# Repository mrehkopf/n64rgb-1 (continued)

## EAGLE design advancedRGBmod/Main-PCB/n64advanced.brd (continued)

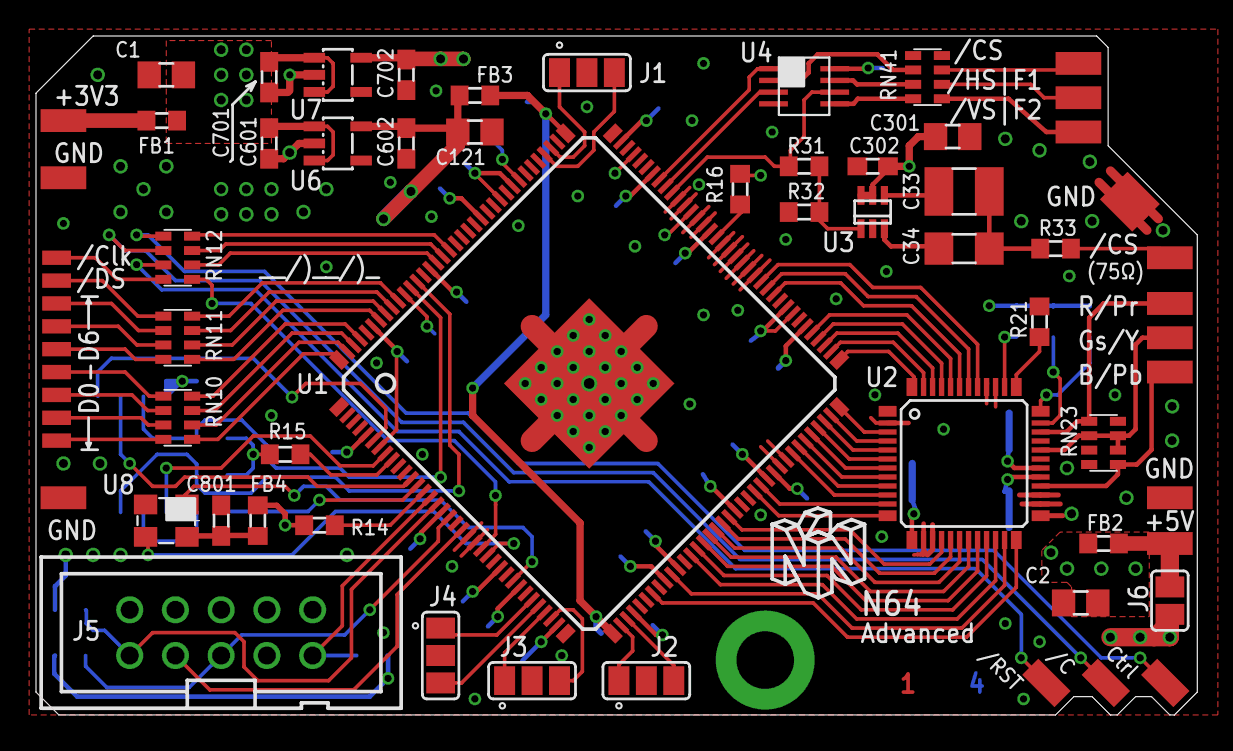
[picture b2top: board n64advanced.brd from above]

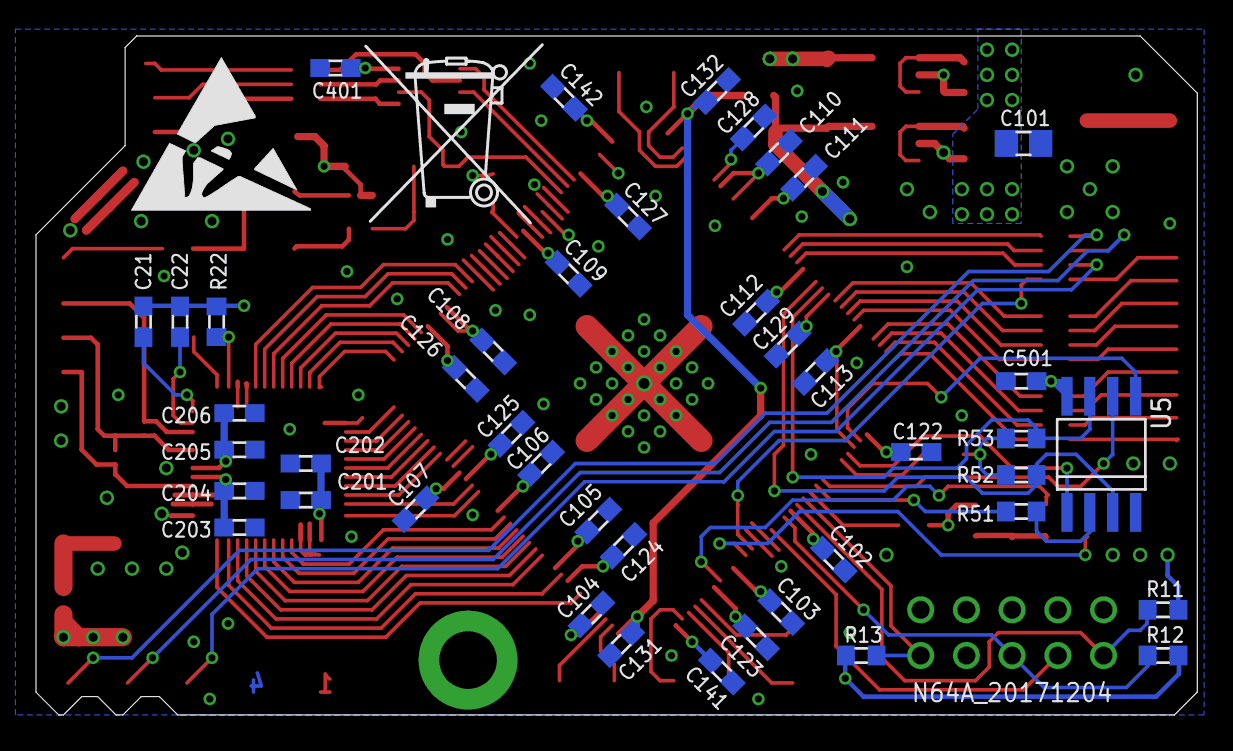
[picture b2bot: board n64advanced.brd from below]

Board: 4 copper layers, 64.5 x 37.7 mm, 112 parts (45 on the bottom side), 105 nets.

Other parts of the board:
U$1: ESD_10.00
U$2: MUELLTONNE_10.00

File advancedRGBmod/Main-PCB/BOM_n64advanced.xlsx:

Designator | MPN | QTY | DESCRIPTION | VALUE | PACKAGE | NOTES | Digikey | Mouser
U1 | 10CL010YE144C8G | 1 | Cyclone 10 LP FPGA, 10k LE |  | EQFP144 | can be replaced with other FPGAs on demand (see Schematic file) | https://www.digikey.de/product-detail/en/altera/10CL010YE144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 | http://www.mouser.de/ProductDetail/Intel/10CL010YE144C8G/
U2 | ADV7125KSTZ140 | 1 | Video DAC 8bit, 3Ch. |  | 48-LQFP | can be replaced with ADV7123KSTZ140 on demand | https://www.digikey.de/product-detail/de/analog-devices-inc/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 | www.mouser.de/ProductDetail/Analog-Devices/ADV7125KSTZ140/
U3 | TSH122ICT | 1 | Video Verstärker 1Ch |  | SC-70-6 |  | https://www.digikey.de/product-detail/de/stmicroelectronics/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 | http://www.mouser.de/ProductDetail/STMicroelectronics/TSH122ICT/
U4 | SN74LVC3G17DCTR | 1 | Non-Inv Buffer 3Ch., Schmitt Trigger |  | 8-LSSOP, 8-MSOP | TI: DCT Package Footprint | https://www.digikey.de/product-detail/de/texas-instruments/S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 | http://www.mouser.de/ProductDetail/Texas-Instruments/SN74LVC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
U5 | S25FL116K0XMFB013 | 1 | IC FLASH 16MBIT 108MHZ 8SOIC |  | 8-SOIC | 208mil Body; Digikey ist Alternative im 150mil Body. Footprint ünterstützt beid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 | https://www.digikey.de/product-detail/de/cypress-semiconduct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 | http://www.mouser.de/ProductDetail/Cypress/S25FL116K0XMFB013/
U6 | TLV70012DDCR | 1 | LDO 1.2V |  | SOT-23-5 |  | https://www.digikey.de/product-detail/de/texas-instruments/T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 | http://www.mouser.de/ProductDetail/Texas-Instruments/TLV70012DDCR/
U7 | TLV70025DDCR | 1 | LDO 2.5V |  | SOT-23-5 |  | https://www.digikey.de/product-detail/de/texas-instruments/T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 | http://www.mouser.de/ProductDetail/Texas-Instruments/TLV70025DDCR/
U8 | ASE-50.000MHZ-LC-T | 1 | OSC 50MHz | 50MHz | 4-SMD | L x B: 0,126" x 0,098" (3,20 mm x 2,50 mm) | https://www.digikey.de/product-detail/de/abracon-llc/ASE-50.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 | http://www.mouser.de/ProductDetail/ABRACON/ASE-50000MHZ-L-C-T/
C1,C2 | GRM219R60J476ME44D | 2 | Ceramic capacitor, X5R | 47uF / 6.3V | SMD0805 |  | https://www.digikey.de/product-detail/de/murata-electronics-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 | http://www.mouser.de/ProductDetail/Murata/GRM219R60J476ME44D/
C21,C22,C102,C103,C104,C105,C106,C107,C108,C109,C110,C111,C112,C113,C122,C123,C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 | GRM188R71H104KA93J | 31 | Ceramic capacitor, X7R | 0.1uF / 50V | SMD0603 |  | https://www.digikey.de/product-detail/de/murata-electronics-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 | http://www.mouser.de/ProductDetail/Murata/GRM188R71H104KA93J/
C101,C121,C301 | GRM21BR60J106ME19L | 3 | Ceramic capacitor, X5R | 10uF / 6.3V | SMD0805 |  | https://www.digikey.de/product-detail/de/murata-electronics-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 | http://www.mouser.de/ProductDetail/Murata/GRM21BR60J106ME19L/
C202,C204,C206,C302,C801 | GRM188R70J103KA01D | 5 | Ceramic capacitor, X7R | 0.01uF / 50V | SMD0603 |  | https://www.digikey.de/product-detail/de/murata-electronics-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 | http://www.mouser.de/ProductDetail/Murata/GRM188R70J103KA01D/
C33 | GRM32DR60J336ME19L | 1 | Ceramic capacitor, X5R | 33uF / 6.3V | SMD1210 |  | https://www.digikey.de/product-detail/de/murata-electronics-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 | http://www.mouser.de/ProductDetail/Murata-Electronics/GRM32D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
C34 | GRM31CR60J226KE19L | 1 | Ceramic capacitor, X5R | 22uF / 6.3V | SMD1206 |  | https://www.digikey.de/product-detail/de/murata-electronics-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 | http://www.mouser.de/ProductDetail/Murata/GRM31CR60J226KE19L/
C601,C602,C701,C702 | GRM18R60J105KA01J | 4 | Ceramic capacitor, X5R | 1uF / 6.3V | SMD0603 |  | https://www.digikey.de/product-detail/de/murata-electronics-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 | https://www.mouser.de/ProductDetail/Murata/GRM188R60J105KA01J/
FB1,FB2,FB3,FB4 | MPZ1608S221A | 4 | Ferrit bead, power line |  | SMD0603 |  | https://www.digikey.de/product-detail/de/tdk-corporation/MPZ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 | http://www.mouser.de/ProductDetail/TDK/MPZ1608S221A/
J5 | 30310-6002HB | 1 |  |  |  | JTAG Connector | https://www.digikey.de/product-detail/de/3m/30310-6002HB/303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 | http://www.mouser.de/ProductDetail/3M/30310-6002HB/
R11 | RC0603FR-071KL | 1 | Resistor | 1k | SMD0603 |  | https://www.digikey.de/product-detail/de/yageo/RC0603FR-071K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 | http://www.mouser.de/ProductDetail/Yageo/RC0603FR-071KL/
R12,R13,R14,R15,R16 | RC0603FR-0710KL | 5 | Resistor | 10k | SMD0603 |  | https://www.digikey.de/product-detail/de/yageo/RC0603FR-0710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 | http://www.mouser.de/ProductDetail/Yageo/RC0603FR-0710KL/
R21 | RC0603FR-07523RL | 1 | Resistor | 518 | SMD0603 | with ADV7123: use 516ohm resistor; for PAL-Standard: 528ohm/527ohm | https://www.digikey.de/product-detail/de/yageo/RC0603FR-0752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 | http://www.mouser.de/ProductDetail/Yageo/RC0603FR-07523RL/
R22,R31,R52,R53 | RC0603FR-074K7L | 4 | Resistor | 4k7 | SMD0603 |  | https://www.digikey.de/product-detail/de/yageo/RC0603FR-074K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 | http://www.mouser.de/ProductDetail/Yageo/RC0603FR-074K7L/
R32 | RC0603FR-07475RL | 1 | Resistor | 475 | SMD0603 |  | https://www.digikey.de/product-detail/de/yageo/RC0603FR-0747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 | http://www.mouser.de/ProductDetail/Yageo/RC0603FR-07475RL/
R33 | RC0603FR-0775RL | 1 | Resistor | 75 | SMD0603 |  | https://www.digikey.de/product-detail/de/yageo/RC0603FR-0775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 | http://www.mouser.de/ProductDetail/Yageo/RC0603FR-0775RL/
R51 | RC0603FR-0724R9L | 1 | Resistor | 25 | SMD0603 |  | https://www.digikey.de/product-detail/de/yageo/RC0603FR-0724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 | http://www.mouser.de/ProductDetail/Yageo/RC0603FR-0724R9L/
RN10,RN11,RN12 | CAT16-47R0F4LF | 3 | Resistor Array (4x) | 47 | SMD1206 | Alternative: CAY16-47R0F4LF | https://www.digikey.de/product-detail/de/bourns-inc/CAT16-47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 | http://www.mouser.de/ProductDetail/Bourns/CAT16-47R0F4LF/
RN23,RN41 | CAT16-75R0F4LF | 2 | Resistor Array (4x) | 75 | SMD1206 | Alternative: CAY16-75R0F4LF; Digi-Key Link zur J4LF Serie (5% Toleranz statt 1%) | https://www.digikey.de/product-detail/de/bourns-inc/CAT16-75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 | http://www.mouser.de/search/ProductDetail.aspx?R=0virtualkey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

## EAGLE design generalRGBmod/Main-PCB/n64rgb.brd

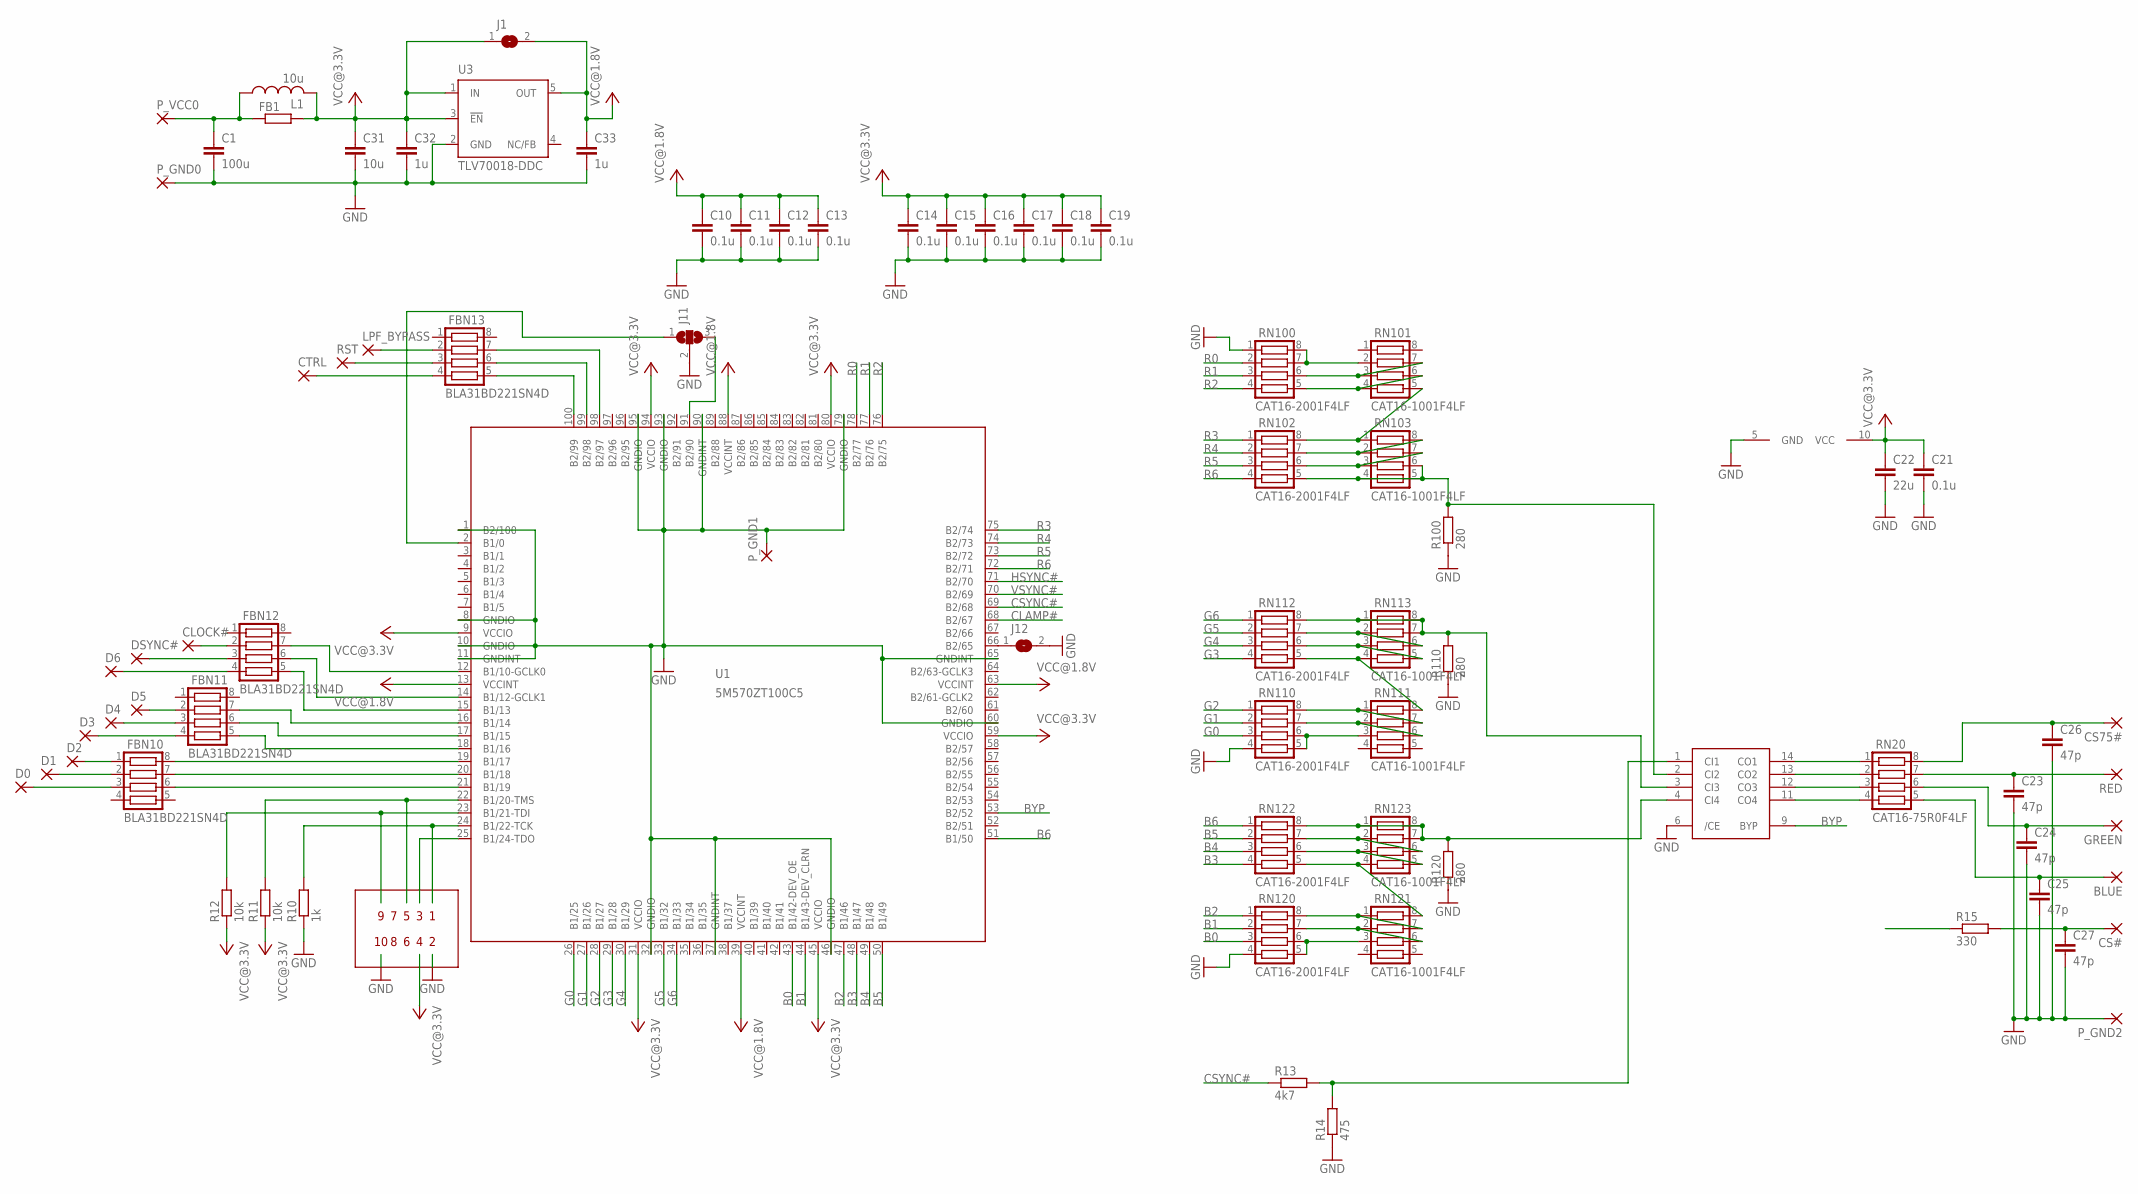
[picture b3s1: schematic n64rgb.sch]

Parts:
BLUE: SMD2; SMD1,27-2,54
C1: 100u; C1206K
C10, C11, C12, C13, C14, C15, C16, C17, C18, C19, C21: 0.1u; C0603
C22: 22u; C1206K
C23, C24, C25, C26, C27: 47p; C0603
C31: 10u; C1206K
C32, C33: 1u; C0603
CLOCK#: SMD1; SMD0,8-1,6
CS75#: SMD2; SMD1,27-2,54
CS#: SMD2; SMD1,27-2,54
CTRL: SMD2; SMD1,27-2,54
D0, D1, D2, D3, D4, D5, D6: SMD1; SMD0,8-1,6
DSYNC#: SMD1; SMD0,8-1,6
FB1: R-EU_R0603; R0603
FBN10, FBN11, FBN12, FBN13: BLA31BD221SN4D; CTS742C083
GREEN: SMD2; SMD1,27-2,54
J1, J12: SJ
J11: SJ2W; SJ_2
L1: 10u; L3230M
LPF_BYPASS: SMD2; SMD1,27-2,54
P_GND0, P_GND1, P_GND2: SMD2; SMD1,27-2,54
P_VCC0: SMD2; SMD1,27-2,54
R10: 1k; R0603
R11, R12: 10k; R0603
R13: 4k7; R0603
R14: 475; R0603
R15: 330; R0603
R100, R110, R120: 280; R0603
RED: SMD2; SMD1,27-2,54
RN20: CAT16-75R0F4LF; CTS742C083
RN100, RN102, RN110, RN112, RN120, RN122: CAT16-2001F4LF; CTS742C083
RN101, RN103, RN111, RN113, RN121, RN123: CAT16-1001F4LF; CTS742C083
RST: SMD2; SMD1,27-2,54
U1: 5M570ZT100C5; TQFP100
U2: THS7374
U3: TLV70018-DDC; SOT23-DBV

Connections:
B0: RN120.3, U1.43 (B1/42-DEV_OE)
B1: RN120.2, U1.44 (B1/43-DEV_CLRN)
B2: RN120.1, U1.47 (B1/46)
B3: RN122.4, U1.48 (B1/47)
B4: RN122.3, U1.49 (B1/48)
B5: RN122.2, U1.50 (B1/49)
B6: RN122.1, U1.51 (B1/50)
BYP: U1.53 (B2/52), U2.9 (BYP)
CLAMP#: U1.68 (B2/67)
CSYNC#: R13.1, R15.1, U1.69 (B2/68)
G0: RN110.3, U1.26 (B1/25)
G1: RN110.2, U1.27 (B1/26)
G2: RN110.1, U1.28 (B1/27)
G3: RN112.4, U1.29 (B1/28)
G4: RN112.3, U1.30 (B1/29)
G5: RN112.2, U1.33 (B1/32)
G6: RN112.1, U1.34 (B1/33)
GND: C1.2, C10.2, C11.2, C12.2, C13.2, C14.2, C15.2, C16.2, C17.2, C18.2, C19.2, C21.2, C22.2, C23.2, C24.2, C25.2, C26.2, C27.2, C31.2, C32.2, C33.2, J11.2, J12.2, P_GND0.1, P_GND1.1, P_GND2.1, R10.1, R14.1, R100.1, R110.1, R120.1, RN100.1, RN110.4, RN120.4, U1.1 (B2/100), U1.8 (GNDIO), U1.10 (GNDIO), U1.11 (GNDINT), U1.32 (GNDIO), U1.37 (GNDINT), U1.46 (GNDIO), U1.60 (GNDIO), U1.65 (GNDINT), U1.79 (GNDIO), U1.90 (GNDINT), U1.93 (GNDIO), U1.95 (GNDIO), U2.5 (GND), U2.6 (/CE), U3.2 (GND)
HSYNC#: U1.71 (B2/70)
unnamed: R13.2, R14.2, U2.1 (CI1)
unnamed: C23.1, RED.1, RN20.7
unnamed: RN20.1, U2.14 (CO1)
unnamed: RN20.2, U2.13 (CO2)
unnamed: RN20.3, U2.12 (CO3)
unnamed: RN20.4, U2.11 (CO4)
unnamed: CTRL.1, FBN13.4
unnamed: FBN13.3, RST.1
unnamed: FBN13.2, LPF_BYPASS.1
unnamed: C24.1, GREEN.1, RN20.6
unnamed: BLUE.1, C25.1, RN20.5
unnamed: C26.1, CS75#.1, RN20.8
unnamed: C27.1, CS#.1, R15.2
unnamed: FBN13.5, U1.100 (B2/99)
unnamed: D1.P$1, FBN10.2
unnamed: D0.P$1, FBN10.3
unnamed: D2.P$1, FBN10.1
unnamed: FBN10.6, U1.21 (B1/19)
unnamed: FBN10.7, U1.20 (B1/18)
unnamed: FBN10.8, U1.19 (B1/17)
unnamed: D3.P$1, FBN11.4
unnamed: D4.P$1, FBN11.3
unnamed: D5.P$1, FBN11.2
unnamed: D6.P$1, FBN12.4
unnamed: RN110.5, RN110.6, RN111.3
unnamed: RN110.7, RN111.2, RN111.6
unnamed: RN110.8, RN111.1, RN111.7
unnamed: RN111.8, RN112.5, RN113.4
unnamed: RN112.6, RN113.3, RN113.5
unnamed: RN112.7, RN113.2, RN113.6
unnamed: R120.2, RN122.8, RN123.1, RN123.7, RN123.8, U2.4 (CI4)
unnamed: RN120.5, RN120.6, RN121.3
unnamed: RN120.7, RN121.2, RN121.6
unnamed: RN120.8, RN121.1, RN121.7
unnamed: RN121.8, RN122.5, RN123.4
unnamed: DSYNC#.P$1, FBN12.3
unnamed: RN122.6, RN123.3, RN123.5
unnamed: RN122.7, RN123.2, RN123.6
unnamed: CLOCK#.P$1, FBN12.2
unnamed: FBN11.5, U1.18 (B1/16)
unnamed: FBN11.6, U1.17 (B1/15)
unnamed: FBN11.7, U1.16 (B1/14)
unnamed: FBN12.5, U1.15 (B1/13)
unnamed: FBN12.6, U1.14 (B1/12-GCLK1)
unnamed: FBN12.7, U1.12 (B1/10-GCLK0)
unnamed: FBN13.6, U1.99 (B2/98)
unnamed: FBN13.7, U1.98 (B2/97)
unnamed: R100.2, RN102.5, RN103.4, RN103.5, RN103.6, U2.2 (CI2)
unnamed: J12.1, U1.66 (B2/65)
unnamed: J11.3, U1.91 (B2/90)
unnamed: J11.1, U1.2 (B1/0)
unnamed: C1.1, FB1.1, L1.1, P_VCC0.1
unnamed: R110.2, RN112.8, RN113.1, RN113.7, RN113.8, U2.3 (CI3)
unnamed: RN100.7, RN100.8, RN101.2
unnamed: RN100.6, RN101.3, RN101.7
unnamed: RN100.5, RN101.4, RN101.6
unnamed: RN101.5, RN102.8, RN103.1
unnamed: RN102.7, RN103.2, RN103.8
unnamed: RN102.6, RN103.3, RN103.7
R0: RN100.2, U1.78 (B2/77)
R1: RN100.3, U1.77 (B2/76)
R2: RN100.4, U1.76 (B2/75)
R3: RN102.1, U1.75 (B2/74)
R4: RN102.2, U1.74 (B2/73)
R5: RN102.3, U1.73 (B2/72)
R6: RN102.4, U1.72 (B2/71)
TCK: R10.2, U1.24 (B1/22-TCK)
TDI: R12.2, U1.23 (B1/21-TDI)
TDO: U1.25 (B1/24-TDO)
TMS: R11.2, U1.22 (B1/20-TMS)
VCC@1.8V: C10.1, C11.1, C12.1, C13.1, C33.1, J1.2, U1.13 (VCCINT), U1.39 (VCCINT), U1.63 (VCCINT), U1.88 (VCCINT), U3.5 (OUT)
VCC@3.3V: C14.1, C15.1, C16.1, C17.1, C18.1, C19.1, C21.1, C22.1, C31.1, C32.1, FB1.2, J1.1, L1.2, R11.1, R12.1, U1.9 (VCCIO), U1.31 (VCCIO), U1.45 (VCCIO), U1.59 (VCCIO), U1.80 (VCCIO), U1.94 (VCCIO), U2.10 (VCC), U3.1 (IN), U3.3 (!EN)
VSYNC#: U1.70 (B2/69)

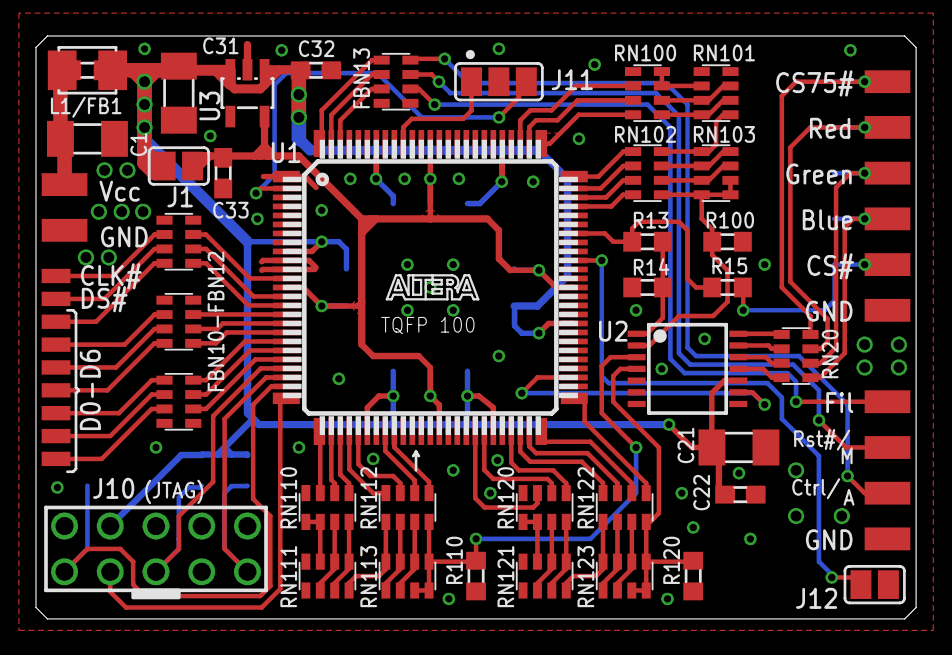
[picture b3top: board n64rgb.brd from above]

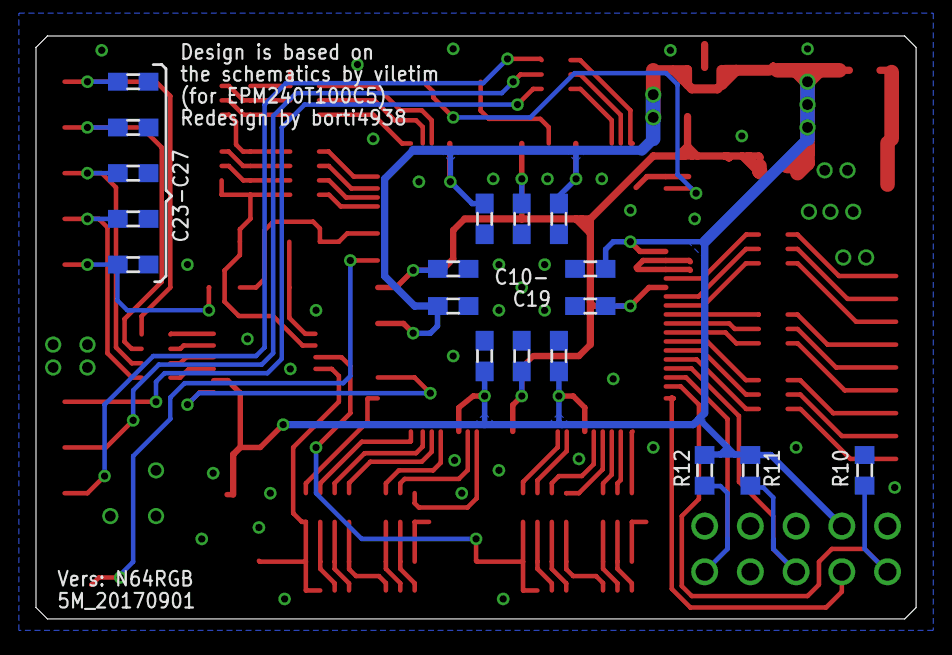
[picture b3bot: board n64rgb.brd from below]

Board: 2 copper layers, 48.9 x 32.4 mm, 76 parts (18 on the bottom side), 88 nets.

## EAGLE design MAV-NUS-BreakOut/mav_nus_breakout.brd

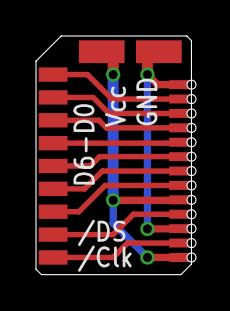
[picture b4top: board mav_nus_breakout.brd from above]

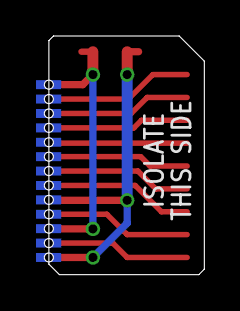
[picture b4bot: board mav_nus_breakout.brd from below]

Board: 2 copper layers, 8.6 x 13.3 mm, 37 parts (13 on the bottom side), 11 nets.

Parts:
PAD13, PAD14: SMD1,27-2,54
U$211, U$212, U$213, U$214, U$215, U$222, U$226, U$227, U$228, U$229, U$230, U$231, U$232, U$233, U$234, U$235, U$236, U$237, U$238, U$239, U$240, U$241, U$242, U$243, U$244, U$245: SMD0,45; SMD0,5-1,4
U$216, U$217, U$218, U$219, U$220, U$221, U$223, U$224, U$225: SMD1; SMD0,8-1,6

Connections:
unnamed: U$211.P$1, U$216.P$1
unnamed: U$217.P$1, U$222.P$1
unnamed: U$218.P$1, U$226.P$1
unnamed: U$219.P$1, U$227.P$1
unnamed: U$220.P$1, U$228.P$1
unnamed: U$221.P$1, U$229.P$1
unnamed: U$223.P$1, U$230.P$1
unnamed: U$224.P$1, U$231.P$1
unnamed: U$225.P$1, U$232.P$1
unnamed: PAD13.1, U$212.P$1, U$213.P$1
unnamed: PAD14.1, U$214.P$1, U$215.P$1

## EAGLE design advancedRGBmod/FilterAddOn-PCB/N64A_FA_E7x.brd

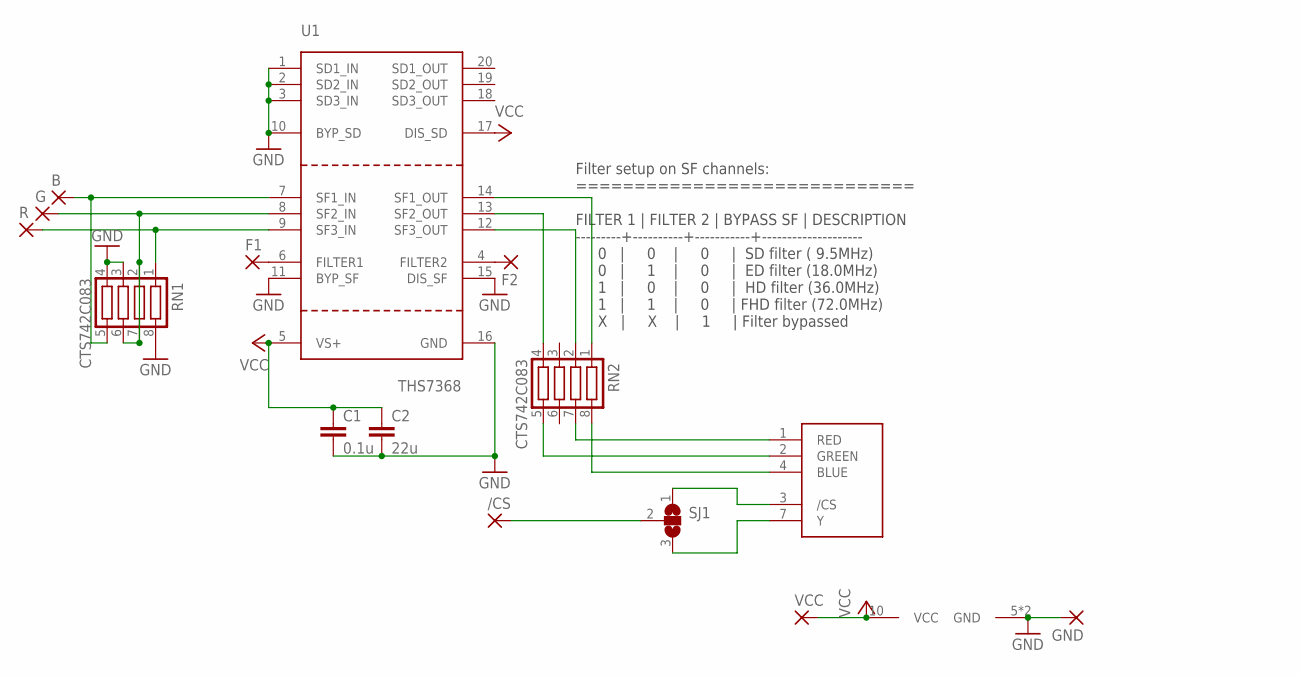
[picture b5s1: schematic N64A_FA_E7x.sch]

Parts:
/CS: SMD2; SMD1,27-2,54
B: SMD2; SMD1,27-2,54
C1: 0.1u; C0603
C2: 22u; C1206
F1, F2: SMD1; SMD0,8-1,6
G: SMD2; SMD1,27-2,54
GND: SMD2; SMD1,27-2,54
R: SMD2; SMD1,27-2,54
RN1, RN2: CTS742C083
SJ1: SJ2W; SJ_2
U1: THS7368
U$1: SNES_MULTIAV_RGBSY
VCC: SMD2; SMD1,27-2,54

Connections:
GND: C1.2, C2.2, GND.1, RN1.3, RN1.4, RN1.8, U1.1 (SD1_IN), U1.2 (SD2_IN), U1.3 (SD3_IN), U1.10 (BYP_SD), U1.11 (BYP_SF), U1.15 (DIS_SF), U1.16 (GND), U$1.5 (GND), U$1.6 (GND)
unnamed: RN2.7, U$1.1 (RED)
unnamed: RN2.8, U$1.4 (BLUE)
unnamed: RN2.5, U$1.2 (GREEN)
unnamed: RN2.4, U1.13 (SF2_OUT)
unnamed: RN2.1, U1.14 (SF1_OUT)
unnamed: RN2.2, U1.12 (SF3_OUT)
unnamed: SJ1.1, U$1.3 (/CS)
unnamed: F1.P$1, U1.6 (FILTER1)
unnamed: R.1, RN1.1, U1.9 (SF3_IN)
unnamed: G.1, RN1.2, RN1.6, RN1.7, U1.8 (SF2_IN)
unnamed: F2.P$1, U1.4 (FILTER2)
unnamed: /CS.1, SJ1.2
unnamed: B.1, RN1.5, U1.7 (SF1_IN)
unnamed: SJ1.3, U$1.7 (Y)
VCC: C1.1, C2.1, U1.5 (VS+), U1.17 (DIS_SD), U$1.10 (VCC), VCC.1

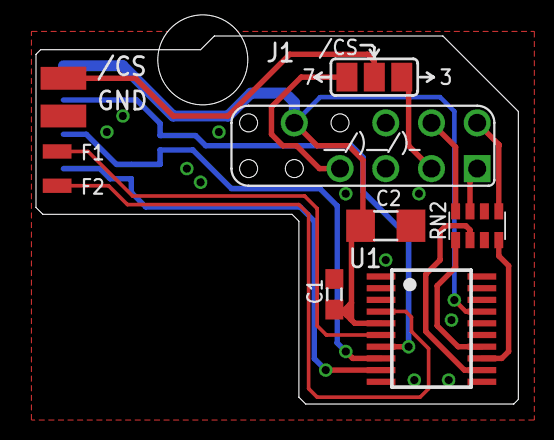
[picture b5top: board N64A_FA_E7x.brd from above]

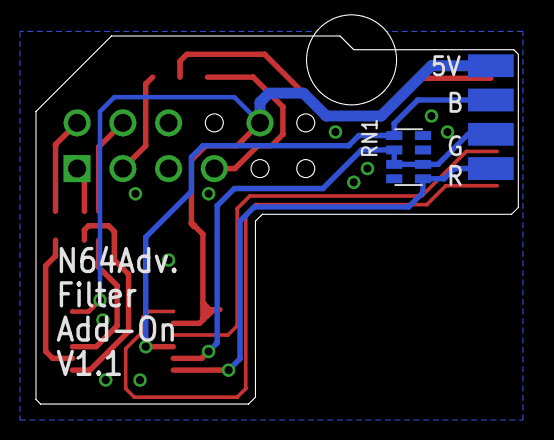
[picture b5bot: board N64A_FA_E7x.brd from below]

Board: 2 copper layers, 26.8 x 20.4 mm, 15 parts (5 on the bottom side), 16 nets.

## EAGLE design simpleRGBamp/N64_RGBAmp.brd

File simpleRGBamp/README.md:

# Simple RGB Mod

## General Information

Technical information about this mod...

- Which N64 is suitable for it
- How to install this mod

... can be found on RetroRGB.com ([Compatibility](http://www.retrorgb.com/n64rgbcompatible.html) and [Installation](http://www.retrorgb.com/n64rgbmod.html))

Many thanks to Bob at this place for sharing that.

The rest

- Which parts are needed
- Some additional tips and hints

can be found in this document.

## Components

**be aware of the additional comments below this table**

| Label | Device / Part | Package | Quantity | Mouser Ordering Key | Comment |
|:---:|---|---|:---:|:---|---|
| | | | | | |
| **U1** | THS7374 | TSSOP-14 | 1 | 595-THS7374IPWR | |
| | THS7373 | TSSOP-14 | 1 | 595-THS7373IPWR | **Alternative** for the THS7374 [1] |
| **C1** | 22uF / 6.3V (tantal) | SMD case B (typical: 3.50mm x 2.80mm) | 1 | 74-593D226X96R3B2TE3 | |
| **C2** | 0.1uF / 50V (10%) | SMD 0603 | 1 | 80-C0603C104K9R | |  
| | | | | | |
| **R1, R41** | 4.7kohm (1%) | SMD 0603 | 2 | 71-CRCW06034K70FKEAH | |
| **R42** | 475ohm (1%) | SMD 0603 | 1 | 71-CRCW0603-475-E3 | csync compatible with 75ohm termination [2,3] |
| | 10.7kohm | SMD 0603 | 1 | 71-CRCW060310K7FKEB | TTL compatible csync [2,3] |
| **C11,C21,C31** | 0.082uF / 25V (10%) | SMD 0603 | 3 | 81-GRM188R71E823KA1D | |
| **R12,R22,R32** | 5.1Mohm (1%) | SMD 0603 | 3 | 71-CRCW06035M10FKEA | |
| | | | | | |
| **R13,R23,R33** | 75ohm (1%) | SMD 0603 | 3 | 71-RCS060375R0FKEA | NTSC-SNES RGB cable setup or direct wiring on RGB wires [4] |
| | 39ohm (1%) | SMD 0603 | 3 | 71-CRCW060339R0FKEAH | PAL-SNES cable setup on RGB wires [4] |
| **C14,C24,C34** | 47pF / 25V (5%) | SMD 0603 | 3 | 77-VJ0603A470JXXPBC | | 
| | | | | | |
| **C43** | tantal 220uF / 6.3V (tantal) | SMD case D (typical: 7.30mm x 4.30mm) | 1 | 74-593D227X96R3D2TE3 | csync compatible with 75ohm termination[2,3] |
| | 330uF / 6.3V (tantal) | SMD case D (typical: 7.30mm x 4.30mm) | 1 | 74-TR3D337K6R3E0100 | /CSYNC compatible with 75ohm termination, **Alternative** to 220uF tantal [2,3] |
| | *free* | | | | TTL compatible /CSYNC, close **J2** [2,3] |
| **R43** | 75ohm (1%) | SMD 0603 | 1 | 71-RCS060375R0FKEA | csync compatible with 75ohm termination [2,3], NTSC-SNES RGB cable setup [4] |
|| 39ohm (1%) | SMD 0603 | 1 | 71-CRCW060339R0FKEAH | /CSYNC compatible with 75ohm termination [2,3], PAL-SNES cable setup on RGB wires [4] |
| | 0ohm | SMD 0603 | 1 | *use a piece of silver wire* |  TTL compatible /CSYNC [2,3] |
| **C44** | 47pF / 25V (5%) | SMD 0603 | 1 | 77-VJ0603A470JXXPBC | [3] | 

### Additional Comments:

##### [1]  
Both ICs are supported. The THS7373 has one SD-video low pass filter (used for /CSYNC) and three HD-video filters (used for R, G and B). The THS7374 has four SD-video filters.  
At the THS7373 the HD-video LPFs can be bypassed and at the THS7374 all four SD-video filters can be bypassed (using J1).

##### [2]
According to your needs, you can design the board such that it outputs 75ohm compatible /CSYNC or TTL /CSYNC. Be aware of the components marked with this note (**R42**, **R43**, **C43/J2** and **C44**).  
If you have a RGB cable build to work with /CSYNC and use this with another (probably) _unmodified_ console, which you use on a 75ohm terminated source, you may have a resistor (and a cap) build in the sync line. Then you must build this modding board here with TTL compatible sync, too.

##### [3]
If you are going to use the stock /CSYNC circuit of the N64 - which I recommend if you have a NUS-CPU-01/02/03 board - you don't need the components **R43**, **C43** and **C44**. Just leave the footprints disassembled.  
**R42** should remain on the modding board (either size; could also be a short) as it holds channel one of the video amp close to GND.

##### [4]
As the N64 does not output RGB by stock, there is no official RGB cable available. A most common method is to refere to the [SNES cable schematics](http://members.optusnet.com.au/eviltim/gamescart/gamescart.htm#snes).

- If you use a NTSC cable cable, **R13**, **R23** and **R33** (and **R43**) has to be 75ohm resistors.
- If you use a PAL cable setup, **R13**, **R23** and **R33** (and **R43**) has to be 39ohm resistors.

## Source the PCB
Choose the PCB service which suits you. Here are some:

- OSHPark: [Link to the PCB](https://oshpark.com/shared_projects/B3Unx78x) (If the PCB was updated and I forgot to update this link, look onto [my profile](https://oshpark.com/profiles/borti4938))
- PCBWay.com: [Link](http://www.pcbway.com/), [Affiliate Link](http://www.pcbway.com/setinvite.aspx?inviteid=10658)

## Installation

A very good installation guide can be found on [RetroRGB.com](http://www.retrorgb.com/n64rgbmod.html).

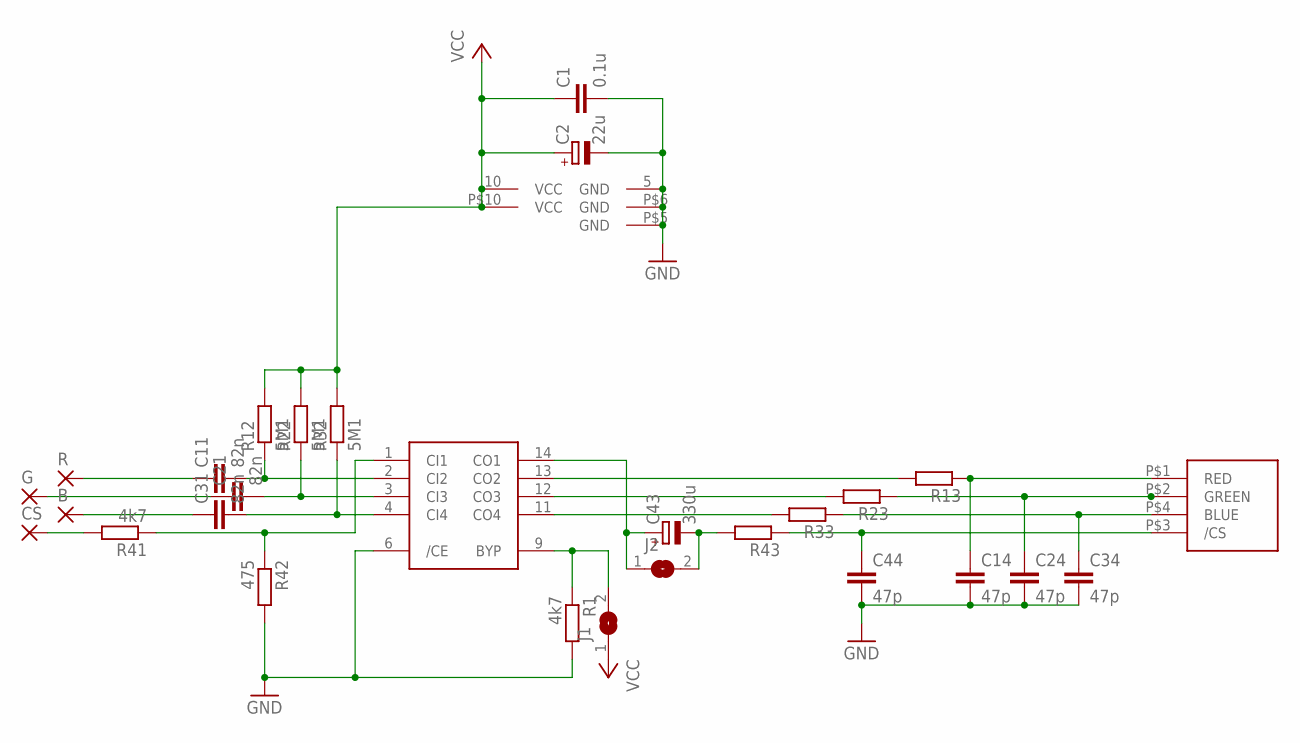
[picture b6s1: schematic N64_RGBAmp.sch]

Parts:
B: SMD2; SMD1,27-2,54
C1: 0.1u; C0603K
C2: 22u; SMC_B
C11, C21, C31: 82n; C0603K
C14, C24, C34, C44: 47p; C0603K
C43: 330u; SMC_D
CS: SMD2; SMD1,27-2,54
G: SMD2; SMD1,27-2,54
J1, J2: SJ
J3: SNES_MULTIAV_RGBC_ONLY
R: SMD2; SMD1,27-2,54
R1, R41: 4k7; R0603
R12, R22, R32: 5M1; R0603
R13, R23, R33, R43: R-EU_R0603; R0603
R42: 475; R0603
U1: THS7374

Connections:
GND: C1.2, C2.-, C14.2, C24.2, C34.2, C44.2, J3.P$5 (GND), J3.P$6 (GND), R1.2, R42.2, U1.5 (GND), U1.6 (/CE)
unnamed: C21.2, R22.1, U1.3 (CI3)
unnamed: R41.1, R42.1, U1.1 (CI1)
unnamed: J1.2, R1.1, U1.9 (BYP)
unnamed: C11.2, R12.1, U1.2 (CI2)
unnamed: C14.1, J3.P$1 (RED), R13.1
unnamed: C24.1, J3.P$2 (GREEN), R23.1
unnamed: R13.2, U1.13 (CO2)
unnamed: R23.2, U1.12 (CO3)
unnamed: C34.1, J3.P$4 (BLUE), R33.1
unnamed: C43.+, J2.1, U1.14 (CO1)
unnamed: R33.2, U1.11 (CO4)
unnamed: C11.1, R.1
unnamed: C21.1, G.1
unnamed: B.1, C31.1
unnamed: CS.1, R41.2
unnamed: C43.-, J2.2, R43.2
unnamed: C44.1, J3.P$3 (/CS), R43.1
R9: C31.2, R32.1, U1.4 (CI4)
VCC: C1.1, C2.+, J1.1, J3.P$10 (VCC), R12.2, R22.2, R32.2, U1.10 (VCC)

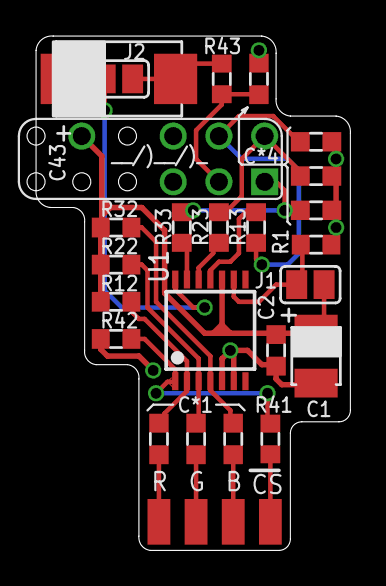
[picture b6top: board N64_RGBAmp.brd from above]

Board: 2 copper layers, 17.5 x 28.6 mm, 28 parts (0 on the bottom side), 20 nets.

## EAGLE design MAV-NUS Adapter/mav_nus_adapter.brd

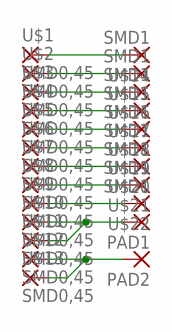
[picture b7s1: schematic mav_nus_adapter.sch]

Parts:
PAD1, PAD2: SMD2; SMD1,27-2,54
U$1, U$2, U$3, U$4, U$5, U$6, U$7, U$8, U$9, U$10, U$11, U$12, U$13: SMD0,45; SMD0,45-1,35
U$14, U$15, U$16, U$17, U$18, U$19, U$20, U$21, U$22: SMD1; SMD0,8-1,6

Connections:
unnamed: U$1.P$1, U$14.P$1
unnamed: U$2.P$1, U$15.P$1
unnamed: U$3.P$1, U$16.P$1
unnamed: U$4.P$1, U$17.P$1
unnamed: U$5.P$1, U$18.P$1
unnamed: U$6.P$1, U$19.P$1
unnamed: U$7.P$1, U$20.P$1
unnamed: U$8.P$1, U$21.P$1
unnamed: U$9.P$1, U$22.P$1
unnamed: PAD1.1, U$10.P$1, U$11.P$1
unnamed: PAD2.1, U$12.P$1, U$13.P$1

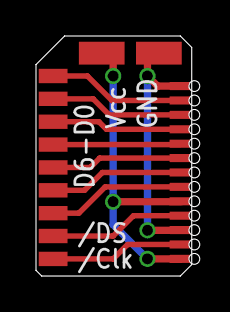
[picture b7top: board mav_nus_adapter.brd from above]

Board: 2 copper layers, 8.7 x 13.3 mm, 24 parts (0 on the bottom side), 11 nets.

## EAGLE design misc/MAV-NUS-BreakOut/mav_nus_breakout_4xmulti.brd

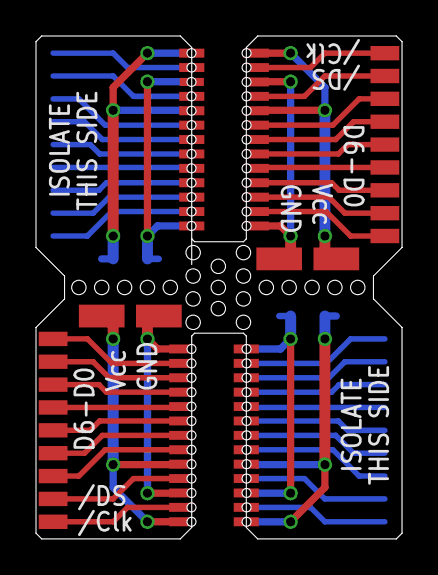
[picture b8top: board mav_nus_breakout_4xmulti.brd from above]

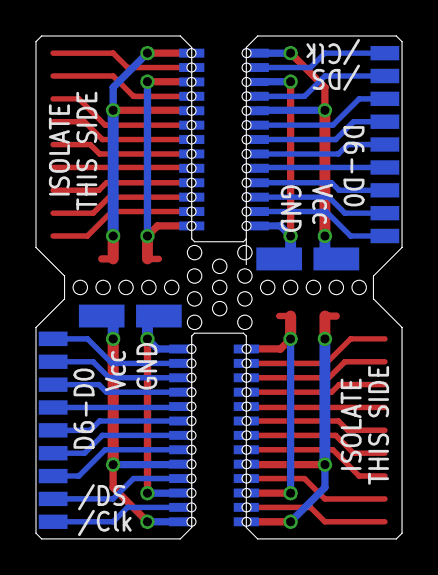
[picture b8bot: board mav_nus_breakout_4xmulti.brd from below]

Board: 2 copper layers, 20.3 x 27.9 mm, 148 parts (74 on the bottom side), 44 nets.

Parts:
PAD3, PAD4, PAD5, PAD6, PAD11, PAD12, PAD13, PAD14: SMD1,27-2,54
U$36, U$37, U$38, U$39, U$40, U$47, U$51, U$52, U$53, U$54, U$55, U$56, U$57, U$58, U$59, U$60, U$61, U$62, U$63, U$64, U$65, U$66, U$67, U$68, U$69, U$70, U$71, U$72, U$73, U$74, U$75, U$82, U$86, U$87, U$88, U$89, U$90, U$91, U$92, U$93, U$94, U$95, U$96, U$97, U$98, U$99, U$100, U$101, U$102, U$103, U$104, U$105, U$176, U$177, U$178, U$180, U$187, U$191, U$192, U$193, U$194, U$195, U$196, U$197, U$198, U$199, U$200, U$201, U$202, U$203, U$204, U$205, U$206, U$207, U$208, U$210, U$211, U$212, U$213, U$214, U$215, U$222, U$226, U$227, U$228, U$229, U$230, U$231, U$232, U$233, U$234, U$235, U$236, U$237, U$238, U$239, U$240, U$241, U$242, U$243, U$244, U$245: SMD0,45; SMD0,5-1,4
U$41, U$42, U$43, U$44, U$45, U$46, U$48, U$49, U$50, U$76, U$77, U$78, U$79, U$80, U$81, U$83, U$84, U$85, U$181, U$182, U$183, U$184, U$185, U$186, U$188, U$189, U$190, U$216, U$217, U$218, U$219, U$220, U$221, U$223, U$224, U$225: SMD1; SMD0,8-1,6
U$179, U$209: SMD0,45; SMD0,45-1,35

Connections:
unnamed: U$36.P$1, U$41.P$1
unnamed: U$42.P$1, U$47.P$1
unnamed: U$43.P$1, U$51.P$1
unnamed: U$44.P$1, U$52.P$1
unnamed: U$45.P$1, U$53.P$1
unnamed: U$46.P$1, U$54.P$1
unnamed: U$48.P$1, U$55.P$1
unnamed: U$49.P$1, U$56.P$1
unnamed: U$50.P$1, U$57.P$1
unnamed: PAD3.1, U$37.P$1, U$38.P$1
unnamed: PAD4.1, U$39.P$1, U$40.P$1
unnamed: U$71.P$1, U$76.P$1
unnamed: U$77.P$1, U$82.P$1
unnamed: U$78.P$1, U$86.P$1
unnamed: U$79.P$1, U$87.P$1
unnamed: U$80.P$1, U$88.P$1
unnamed: U$81.P$1, U$89.P$1
unnamed: U$83.P$1, U$90.P$1
unnamed: U$84.P$1, U$91.P$1
unnamed: U$85.P$1, U$92.P$1
unnamed: PAD5.1, U$72.P$1, U$73.P$1
unnamed: PAD6.1, U$74.P$1, U$75.P$1
unnamed: U$176.P$1, U$181.P$1
unnamed: U$182.P$1, U$187.P$1
unnamed: U$183.P$1, U$191.P$1
unnamed: U$184.P$1, U$192.P$1
unnamed: U$185.P$1, U$193.P$1
unnamed: U$186.P$1, U$194.P$1
unnamed: U$188.P$1, U$195.P$1
unnamed: U$189.P$1, U$196.P$1
unnamed: U$190.P$1, U$197.P$1
unnamed: PAD11.1, U$177.P$1, U$178.P$1
unnamed: PAD12.1, U$179.P$1, U$180.P$1
unnamed: U$211.P$1, U$216.P$1
unnamed: U$217.P$1, U$222.P$1
unnamed: U$218.P$1, U$226.P$1
unnamed: U$219.P$1, U$227.P$1
unnamed: U$220.P$1, U$228.P$1
unnamed: U$221.P$1, U$229.P$1
unnamed: U$223.P$1, U$230.P$1
unnamed: U$224.P$1, U$231.P$1
unnamed: U$225.P$1, U$232.P$1
unnamed: PAD13.1, U$212.P$1, U$213.P$1
unnamed: PAD14.1, U$214.P$1, U$215.P$1
